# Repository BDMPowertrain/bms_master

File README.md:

<h1 align="center">BMS_MASTER</h1>
<p align="center">BMS Master</p>
<p align="center"><em>The BMS master board is the bridge between the TIM and the 16 BMS slave boards. It passes data both ways over a looped daisy chain, isolated by transformers so the battery’s high voltage never reaches the low-voltage side, and it signals the TIM the moment any slave reports a fault.</em></p>

<p align="center" width="100%">
  
</p>

***

<p align="center">
  
&nbsp; &nbsp; &nbsp; &nbsp;
  
</p>

***

## SPECIFICATIONS

| Parameter | Value |
| --- | --- |
| Dimensions | 100.0 × 50.0 mm |
| Company | Blue Devil Motor Sports |
| Designer | Aidan Brzezinski |
| Revision | + (Unreleased) |

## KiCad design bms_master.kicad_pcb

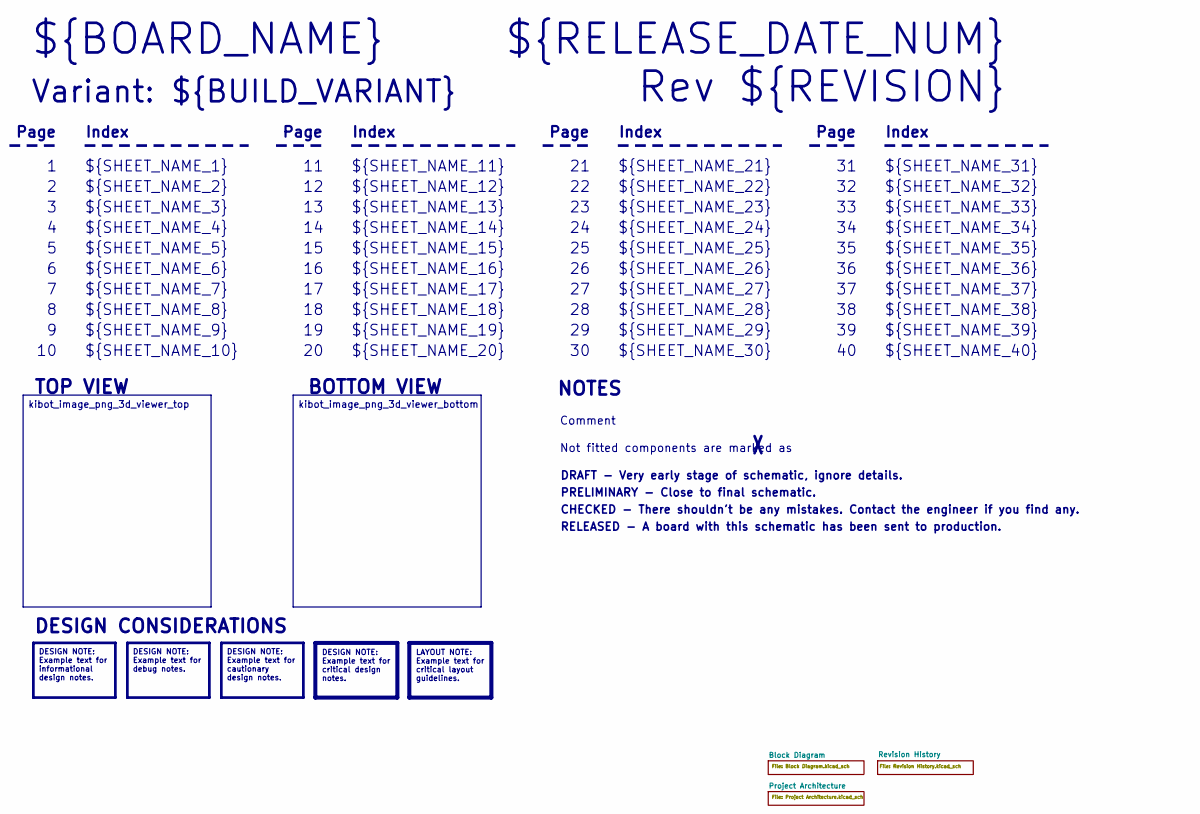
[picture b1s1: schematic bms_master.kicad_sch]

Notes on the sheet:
Variant: ${BUILD_VARIANT}
RELEASED - A board with this schematic has been sent to production.
${SHEET_NAME_24}
Index
Page
PRELIMINARY - Close to final schematic.
${SHEET_NAME_22}
DRAFT - Very early stage of schematic, ignore details.
${SHEET_NAME_12}
${SHEET_NAME_8}
${SHEET_NAME_2}
${SHEET_NAME_5}
${SHEET_NAME_20}
${SHEET_NAME_23}
${RELEASE_DATE_NUM}
${SHEET_NAME_35}
Not fitted components are marked as
${SHEET_NAME_11}
${SHEET_NAME_6}
${SHEET_NAME_37}
${SHEET_NAME_26}
${SHEET_NAME_36}
Rev ${REVISION}
${SHEET_NAME_15}
CHECKED - There shouldn't be any mistakes. Contact the engineer if you find any.
BOTTOM VIEW
${SHEET_NAME_14}
${SHEET_NAME_21}
${SHEET_NAME_17}
${SHEET_NAME_18}
${SHEET_NAME_7}
${SHEET_NAME_31}
${BOARD_NAME}
NOTES
${SHEET_NAME_40}
${SHEET_NAME_39}
${SHEET_NAME_32}
${SHEET_NAME_1}
${SHEET_NAME_9}
${SHEET_NAME_38}

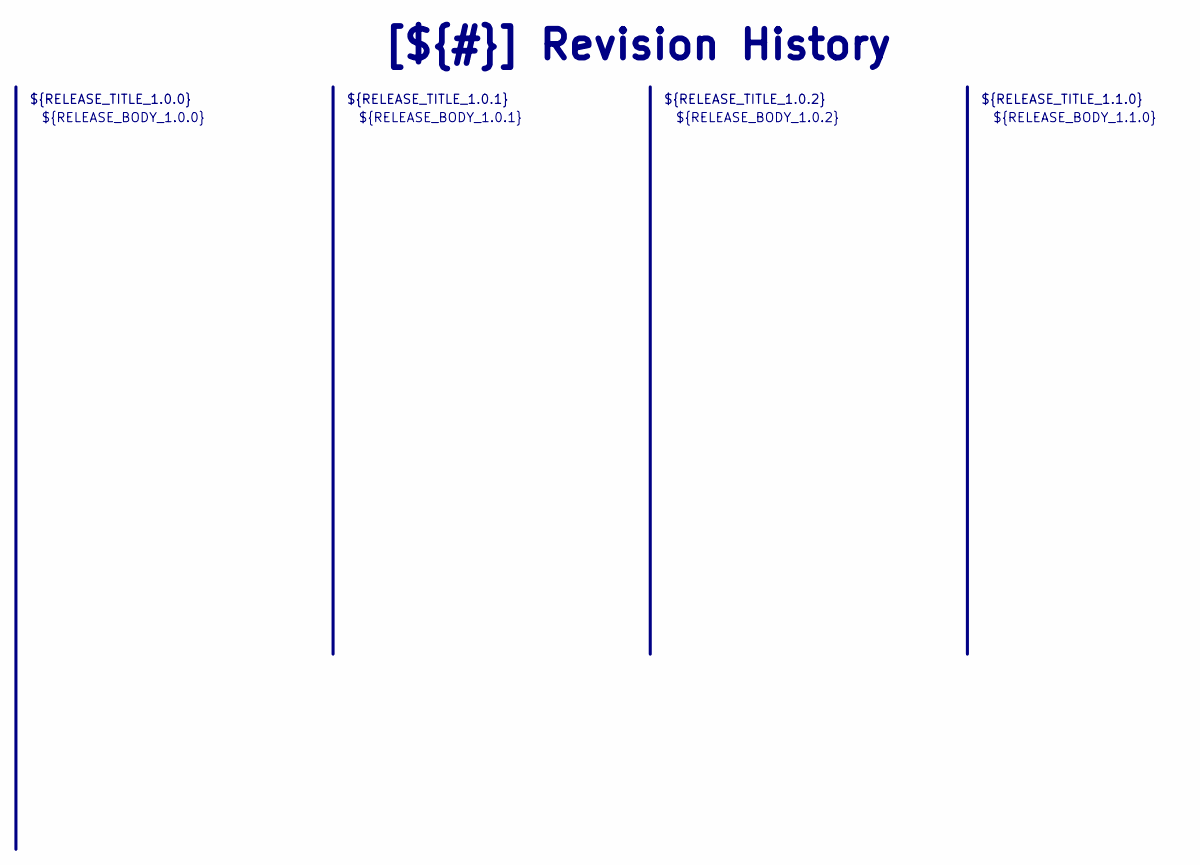
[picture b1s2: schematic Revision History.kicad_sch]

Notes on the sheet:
${RELEASE_BODY_1.1.0}
[${#}] ${TITLE}
${RELEASE_BODY_1.0.0}
${RELEASE_TITLE_1.0.2}
${RELEASE_BODY_1.0.2}
${RELEASE_BODY_1.0.1}
${RELEASE_TITLE_1.0.0}
${RELEASE_TITLE_1.0.1}
${RELEASE_TITLE_1.1.0}

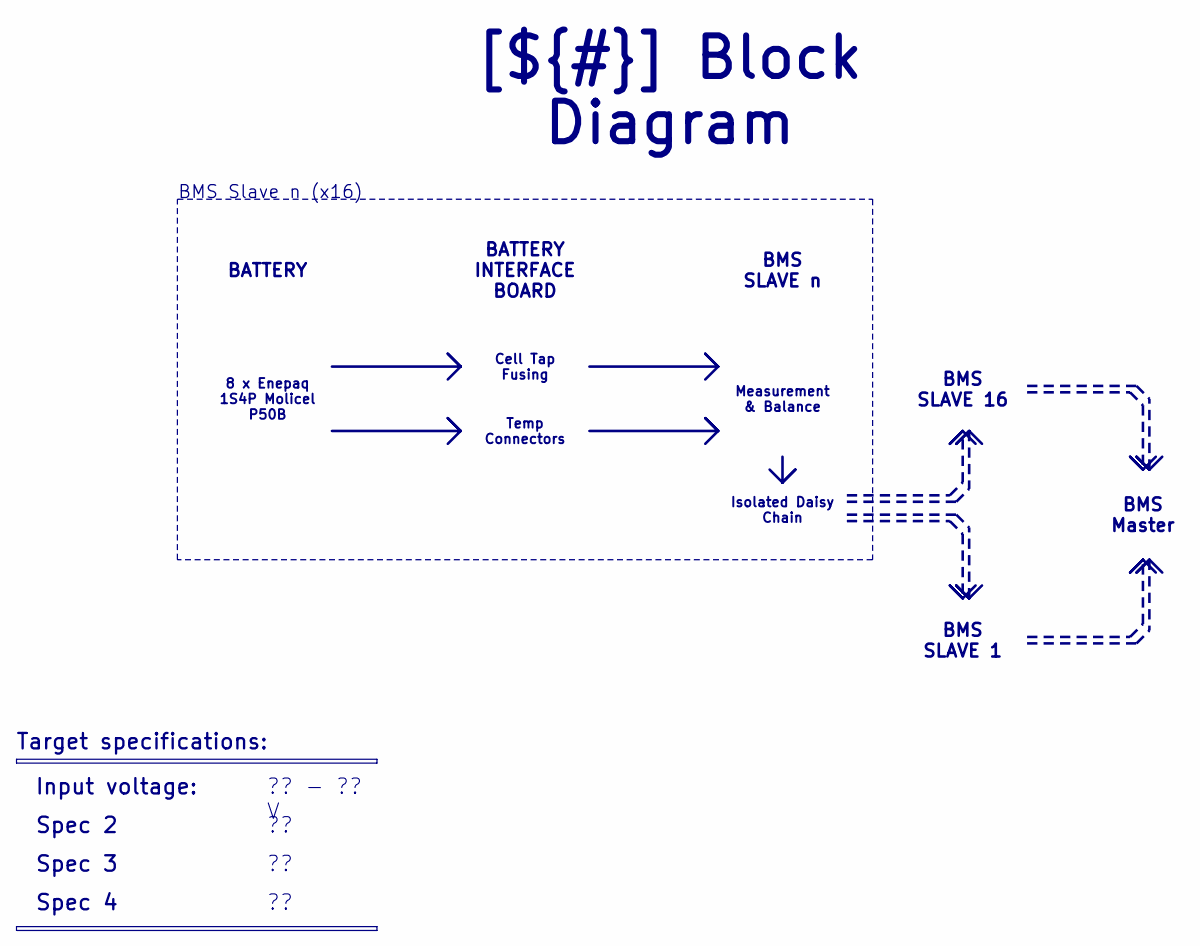
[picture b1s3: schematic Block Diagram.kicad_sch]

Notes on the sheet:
BMS Slave n (x16)
Spec 4
?? - ?? V
Isolated Daisy Chain
Cell Tap Fusing
8 x Enepaq 1S4P Molicel P50B
Temp Connectors
[${#}] ${TITLE}
Input voltage:
Target specifications:
BMS Master
Measurement & Balance
Spec 3
Spec 2
BATTERY
BMS SLAVE n
BMS SLAVE 16
BATTERY INTERFACE BOARD
BMS SLAVE 1

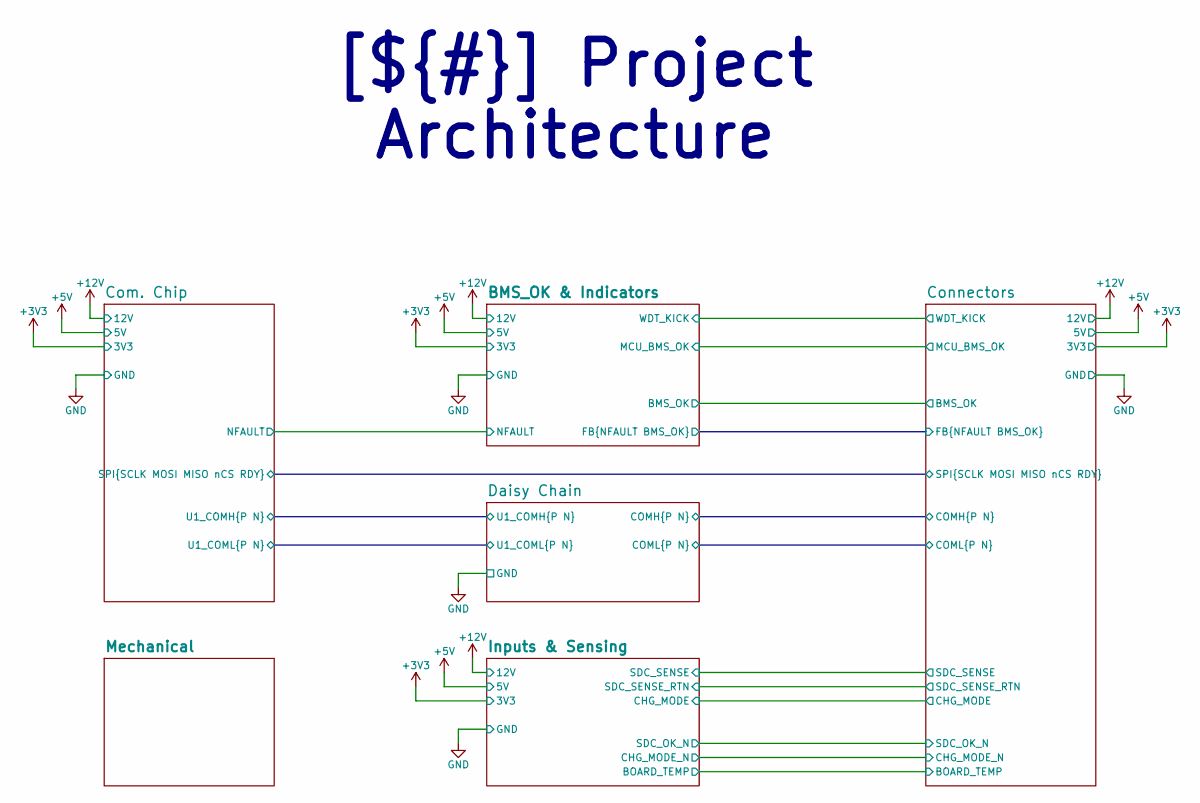
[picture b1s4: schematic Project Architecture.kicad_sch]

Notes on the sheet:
[${#}] ${TITLE}

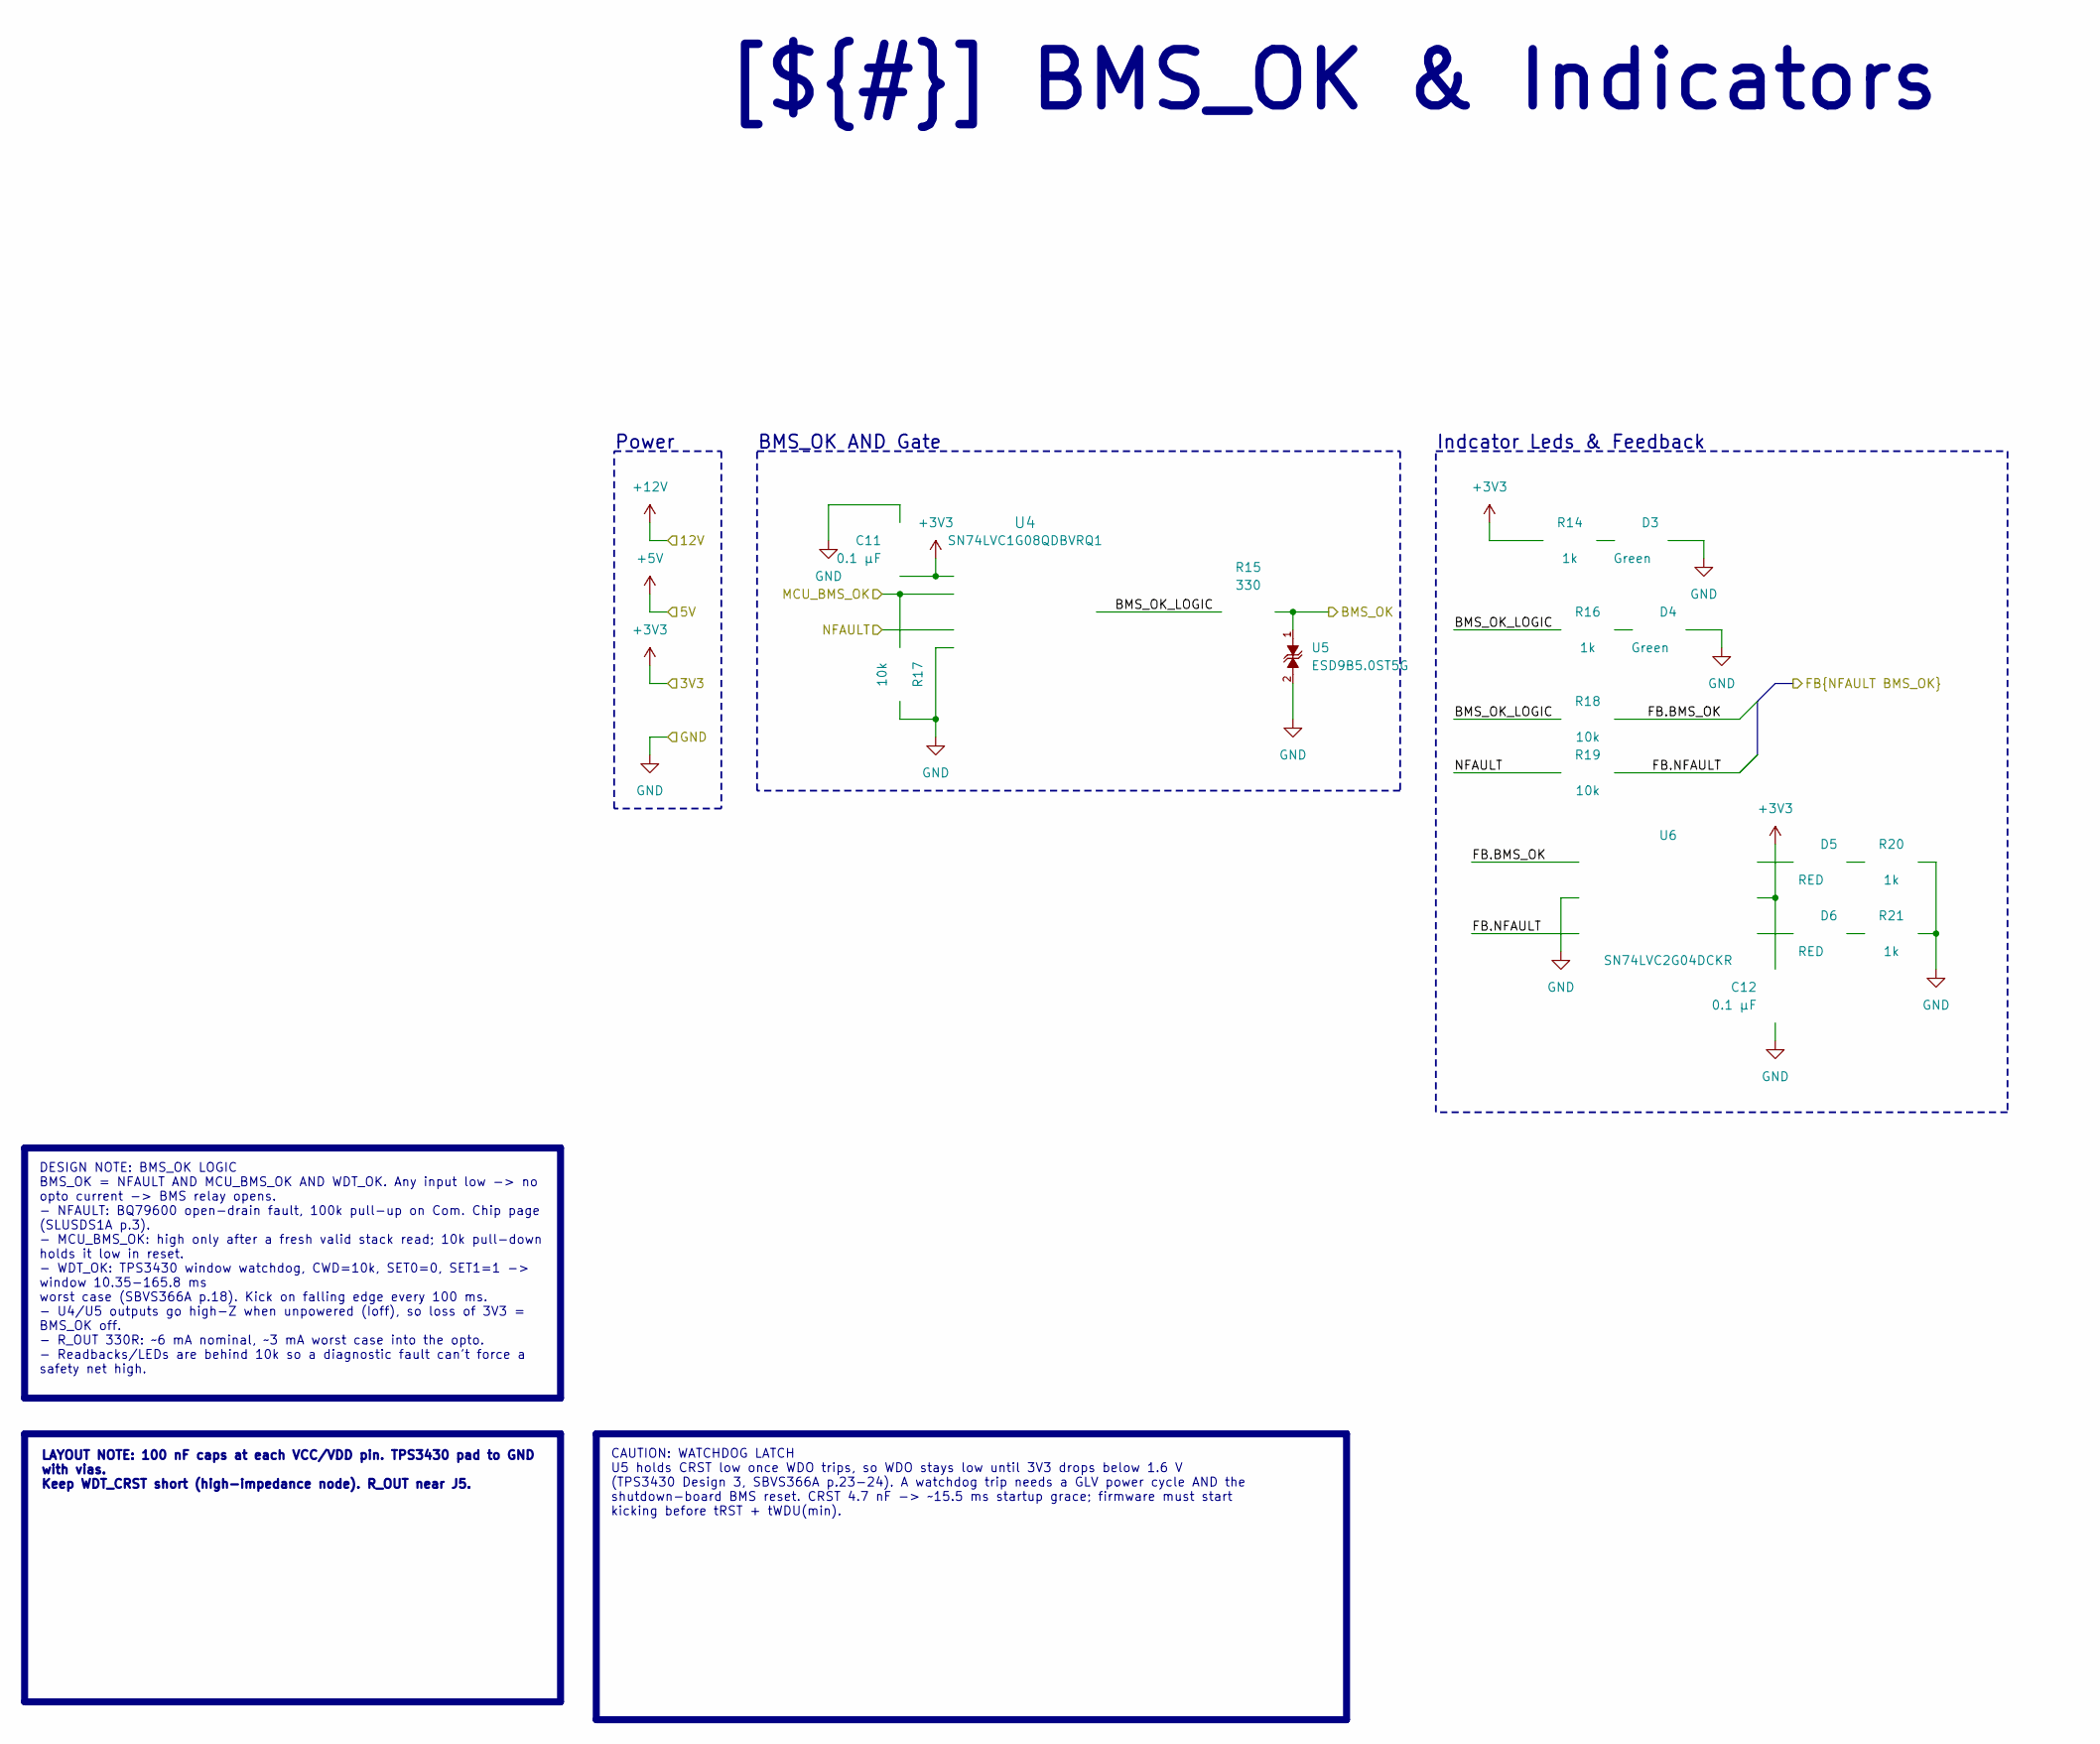
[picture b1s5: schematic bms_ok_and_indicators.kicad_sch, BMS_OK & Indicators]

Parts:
C11, C12: 0.1 µF; C_0402_1005Metric; Manufacturer Part Number GCM155R71H104KE02J
D3, D4: Green; LED_0603_1608Metric; Manufacturer Part Number LTST-C190KGKT
D5, D6: RED; LED_0603_1608Metric; Manufacturer Part Number LTST-C190KRKT
R14, R16, R20, R21: 1k; R_0402_1005Metric; Manufacturer Part Number ERJ-2RKF1001X
R15: 330; R_0805_2012Metric; Manufacturer Part Number CRCW0805330RFKEA
R17, R18, R19: 10k; R_0402_1005Metric; Manufacturer Part Number RC0402JR-0710KL
U4: SN74LVC1G08QDBVRQ1; DBV5; Manufacturer Part Number SN74LVC1G08QDBVRQ1
U5: ESD9B5.0ST5G; SODFL1006X40N; Manufacturer Part Number ESD9B5.0ST5G
U6: SN74LVC2G04DCKR; DCK0006A_N; Manufacturer Part Number SN74LVC2G04DCKR

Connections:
/Project Architecture/+3V3: C11.1, C12.2, R14.2, U4.5 (VCC), U6.5 (VCC); also elsewhere on the board
/Project Architecture/BMS_OK & Indicators/BMS_OK: R15.2, U5.1; also elsewhere on the board
/Project Architecture/BMS_OK & Indicators/BMS_OK_LOGIC: R15.1, R16.2, R18.1, U4.4 (Y)
/Project Architecture/BMS_OK & Indicators/FB.BMS_OK: R18.2, U6.1 (1A); also elsewhere on the board
/Project Architecture/BMS_OK & Indicators/FB.NFAULT: R19.2, U6.3 (2A); also elsewhere on the board
/Project Architecture/BMS_OK & Indicators/NFAULT: R19.1, U4.2 (B); also elsewhere on the board
/Project Architecture/Connectors/MCU_BMS_OK: R17.1, U4.1 (A); also elsewhere on the board
/Project Architecture/GND: C11.2, C12.1, D3.1 (K), D4.1 (K), R17.2, R20.1, R21.1, U4.3 (GND), U5.2, U6.2 (GND); also elsewhere on the board
unnamed: D3.2 (A), R14.1
unnamed: D4.2 (A), R16.1
unnamed: D5.2 (A), U6.6 (1Y)
unnamed: D5.1 (K), R20.2
unnamed: D6.2 (A), U6.4 (2Y)
unnamed: D6.1 (K), R21.2

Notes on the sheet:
BMS_OK AND Gate
Indcator Leds & Feedback
Power
[${#}] ${TITLE}
LAYOUT NOTE: 100 nF caps at each VCC/VDD pin. TPS3430 pad to GND with vias. Keep WDT_CRST short (high-impedance node). R_OUT near J5.
DESIGN NOTE: BMS_OK LOGIC BMS_OK = NFAULT AND MCU_BMS_OK AND WDT_OK. Any input low -> no opto current -> BMS relay opens. - NFAULT: BQ79600 open-drain fault, 100k pull-up on Com. Chip page (SLUSDS1A p.3). - MCU_BMS_OK: high only after a fresh valid stack read; 10k pull-down holds it low in reset. -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
CAUTION: WATCHDOG LATCH U5 holds CRST low once WDO trips, so WDO stays low until 3V3 drops below 1.6 V (TPS3430 Design 3, SBVS366A p.23-24). A watchdog trip needs a GLV power cycle AND the shutdown-board BMS reset. CRST 4.7 nF -> ~15.5 ms startup grace; firmware must start kicking before tRST + tWD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

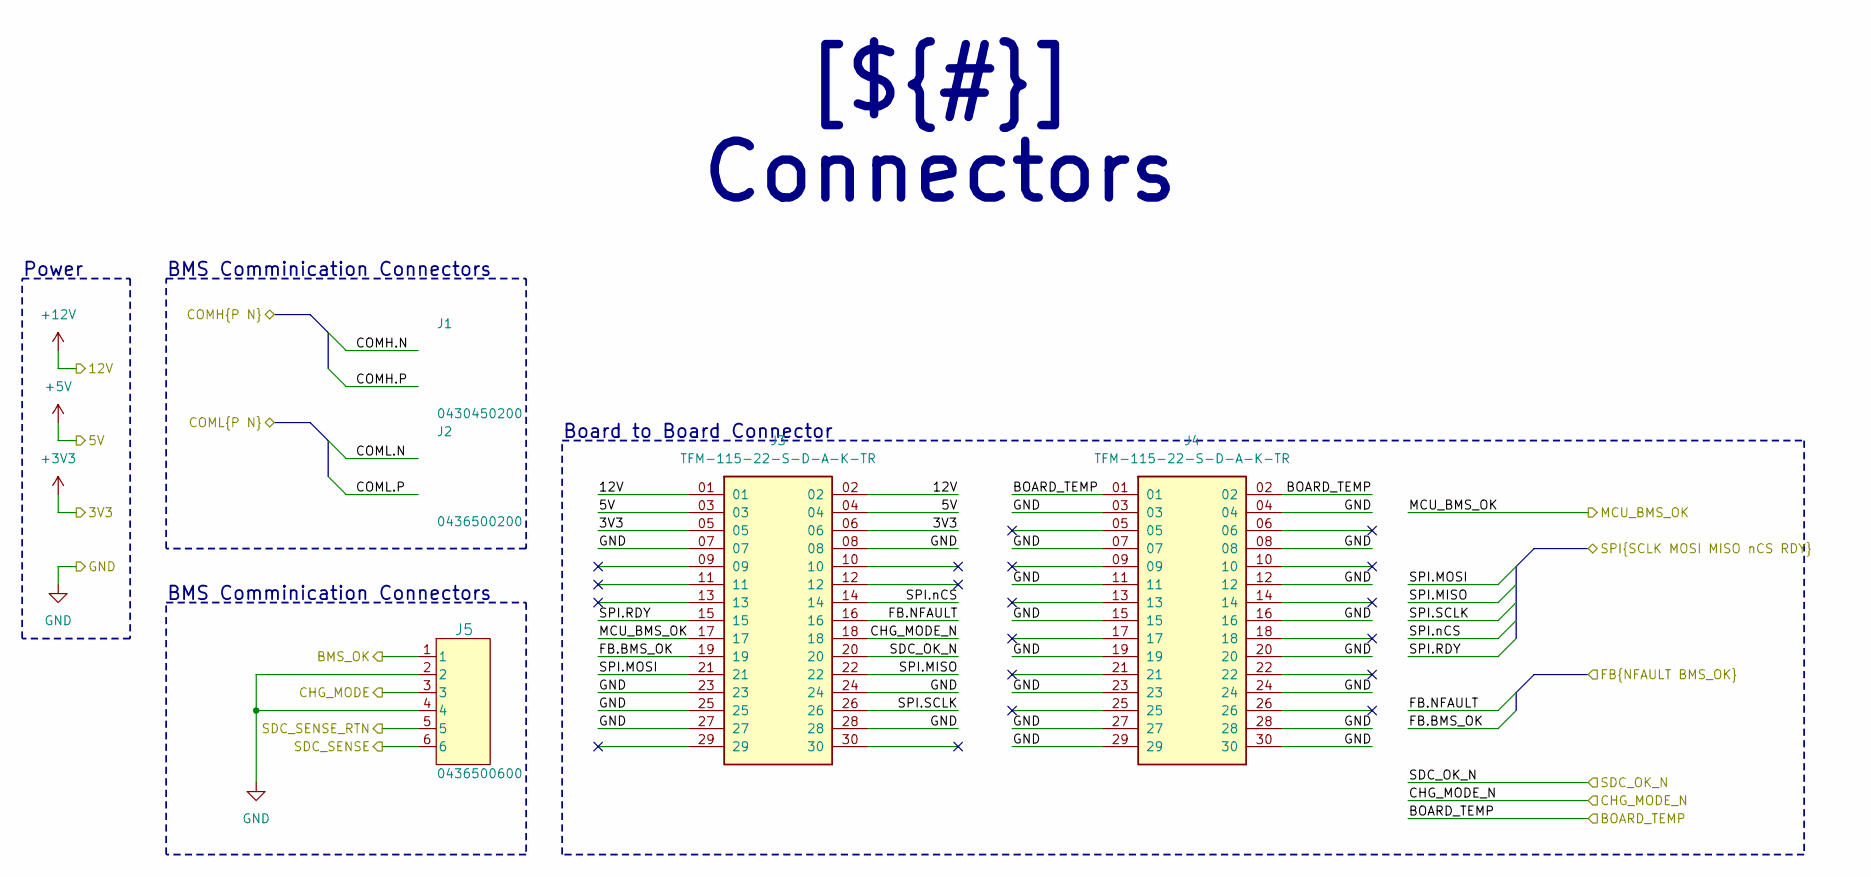
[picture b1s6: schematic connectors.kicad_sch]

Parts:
J1: 0430450200; CONN_SD-43045-001_02_MOL; Manufacturer Part Number 0430450200
J2: 0436500200; CONN_SD-43650-001_02_MOL; Manufacturer Part Number 0436500200
J3, J4: TFM-115-22-S-D-A-K-TR; SAMTEC_TFM-115-22-S-D-A; PARTREV R
J5: 0436500600; CONN_SD-43650-001_06_MOL; Manufacturer Part Number 0436500600

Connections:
/Project Architecture/+3V3: J3.05, J3.06; also elsewhere on the board
/Project Architecture/+5V: J3.03, J3.04
/Project Architecture/+12V: J3.01, J3.02; also elsewhere on the board
/Project Architecture/BMS_OK & Indicators/BMS_OK: J5.1; also elsewhere on the board
/Project Architecture/BMS_OK & Indicators/FB.BMS_OK: J3.19; also elsewhere on the board
/Project Architecture/BMS_OK & Indicators/FB.NFAULT: J3.16; also elsewhere on the board
/Project Architecture/Com. Chip/SPI.MISO: J3.22; also elsewhere on the board
/Project Architecture/Com. Chip/SPI.MOSI: J3.21; also elsewhere on the board
/Project Architecture/Com. Chip/SPI.RDY: J3.15; also elsewhere on the board
/Project Architecture/Com. Chip/SPI.SCLK: J3.26; also elsewhere on the board
/Project Architecture/Com. Chip/SPI.nCS: J3.14; also elsewhere on the board
/Project Architecture/Connectors/BOARD_TEMP: J4.01, J4.02; also elsewhere on the board
/Project Architecture/Connectors/CHG_MODE: J5.3; also elsewhere on the board
/Project Architecture/Connectors/CHG_MODE_N: J3.18; also elsewhere on the board
/Project Architecture/Connectors/COMH.N: J1.1; also elsewhere on the board
/Project Architecture/Connectors/COMH.P: J1.2; also elsewhere on the board
/Project Architecture/Connectors/COML.N: J2.1; also elsewhere on the board
/Project Architecture/Connectors/COML.P: J2.2; also elsewhere on the board
/Project Architecture/Connectors/MCU_BMS_OK: J3.17; also elsewhere on the board
/Project Architecture/Connectors/SDC_OK_N: J3.20; also elsewhere on the board
/Project Architecture/Connectors/SDC_SENSE: J5.6; also elsewhere on the board
/Project Architecture/Connectors/SDC_SENSE_RTN: J5.5; also elsewhere on the board
/Project Architecture/GND: J3.07, J3.08, J3.23, J3.24, J3.25, J3.27, J3.28, J4.03, J4.04, J4.07, J4.08, J4.11, J4.12, J4.15, J4.16, J4.19, J4.20, J4.23, J4.24, J4.27, J4.28, J4.29, J4.30, J5.2, J5.4; also elsewhere on the board

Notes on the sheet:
Power
BMS Comminication Connectors
Board to Board Connector
[${#}] ${TITLE}

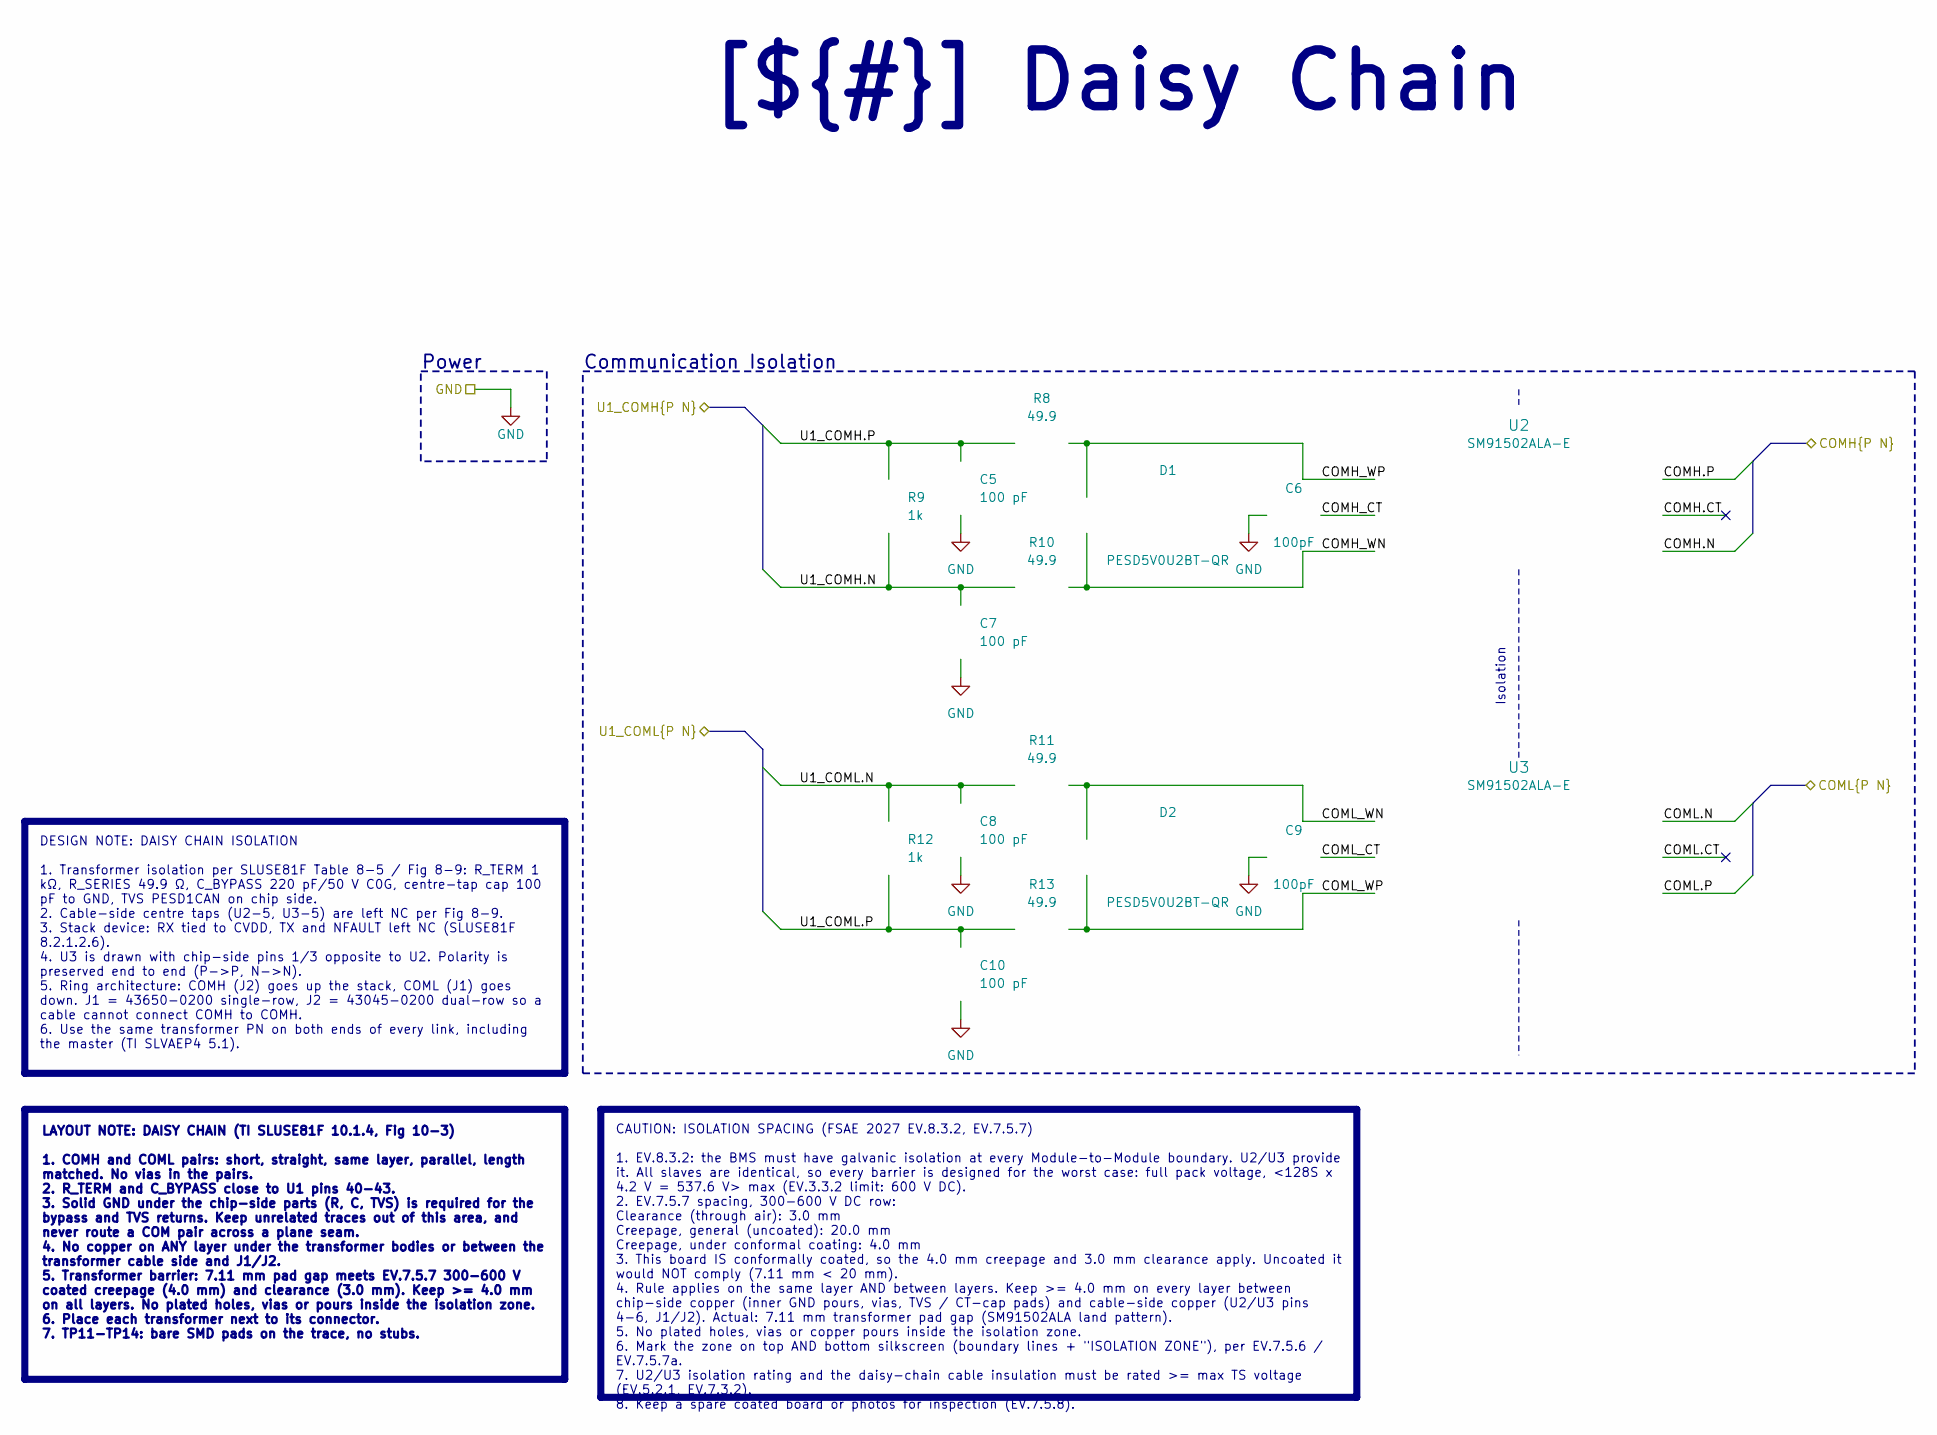
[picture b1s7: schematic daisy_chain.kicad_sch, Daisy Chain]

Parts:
C5, C7, C8, C10: 100 pF; C_0402_1005Metric; Manufacturer Part Number GCM1555C1H101JA16D
C6, C9: 100pF; C_0402_1005Metric; Manufacturer Part Number GCM1555C1H101JA16D
D1, D2: PESD5V0U2BT-QR; SOT-23-3; Manufacturer Part Number PESD5V0U2BT-QR
R8, R10, R11, R13: 49.9; R_0402_1005Metric; Manufacturer Part Number CRCW040249R9FKED
R9, R12: 1k; R_0402_1005Metric; Manufacturer Part Number ERJ-2RKF1001X
U2, U3: SM91502ALA-E; IC6_SM91502ALA-E_BRN; Manufacturer Part Number SM91502ALA-E

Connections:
/Project Architecture/Com. Chip/U1_COMH.N: C7.2, R9.2, R10.1; also elsewhere on the board
/Project Architecture/Com. Chip/U1_COMH.P: C5.2, R8.1, R9.1; also elsewhere on the board
/Project Architecture/Com. Chip/U1_COML.N: C8.2, R11.1, R12.1; also elsewhere on the board
/Project Architecture/Com. Chip/U1_COML.P: C10.2, R12.2, R13.1; also elsewhere on the board
/Project Architecture/Connectors/COMH.N: U2.4; also elsewhere on the board
/Project Architecture/Connectors/COMH.P: U2.6; also elsewhere on the board
/Project Architecture/Connectors/COML.N: U3.6; also elsewhere on the board
/Project Architecture/Connectors/COML.P: U3.4; also elsewhere on the board
/Project Architecture/Daisy Chain/COMH.CT: U2.5
/Project Architecture/Daisy Chain/COMH_CT: C6.1, U2.2
/Project Architecture/Daisy Chain/COMH_WN: D1.2, R10.2, U2.3
/Project Architecture/Daisy Chain/COMH_WP: D1.1, R8.2, U2.1
/Project Architecture/Daisy Chain/COML.CT: U3.5
/Project Architecture/Daisy Chain/COML_CT: C9.1, U3.2
/Project Architecture/Daisy Chain/COML_WN: D2.1, R11.2, U3.1
/Project Architecture/Daisy Chain/COML_WP: D2.2, R13.2, U3.3
/Project Architecture/GND: C5.1, C6.2, C7.1, C8.1, C9.2, C10.1, D1.3, D2.3; also elsewhere on the board

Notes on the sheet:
Isolation
Communication Isolation
Power
[${#}] ${TITLE}
CAUTION: ISOLATION SPACING (FSAE 2027 EV.8.3.2, EV.7.5.7) 1. EV.8.3.2: the BMS must have galvanic isolation at every Module-to-Module boundary. U2/U3 provide it. All slaves are identical, so every barrier is designed for the worst case: full pack voltage, <128S x 4.2 V = 537.6 V> max (EV.3.3.2 limi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
DESIGN NOTE: DAISY CHAIN ISOLATION 1. Transformer isolation per SLUSE81F Table 8-5 / Fig 8-9: R_TERM 1 kΩ, R_SERIES 49.9 Ω, C_BYPASS 220 pF/50 V C0G, centre-tap cap 100 pF to GND, TVS PESD1CAN on chip side. 2. Cable-side centre taps (U2-5, U3-5) are left NC per Fig 8-9. 3. Stack device: RX tied to 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
LAYOUT NOTE: DAISY CHAIN (TI SLUSE81F 10.1.4, Fig 10-3) 1. COMH and COML pairs: short, straight, same layer, parallel, length matched. No vias in the pairs. 2. R_TERM and C_BYPASS close to U1 pins 40-43. 3. Solid GND under the chip-side parts (R, C, TVS) is required for the bypass and TVS returns. 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

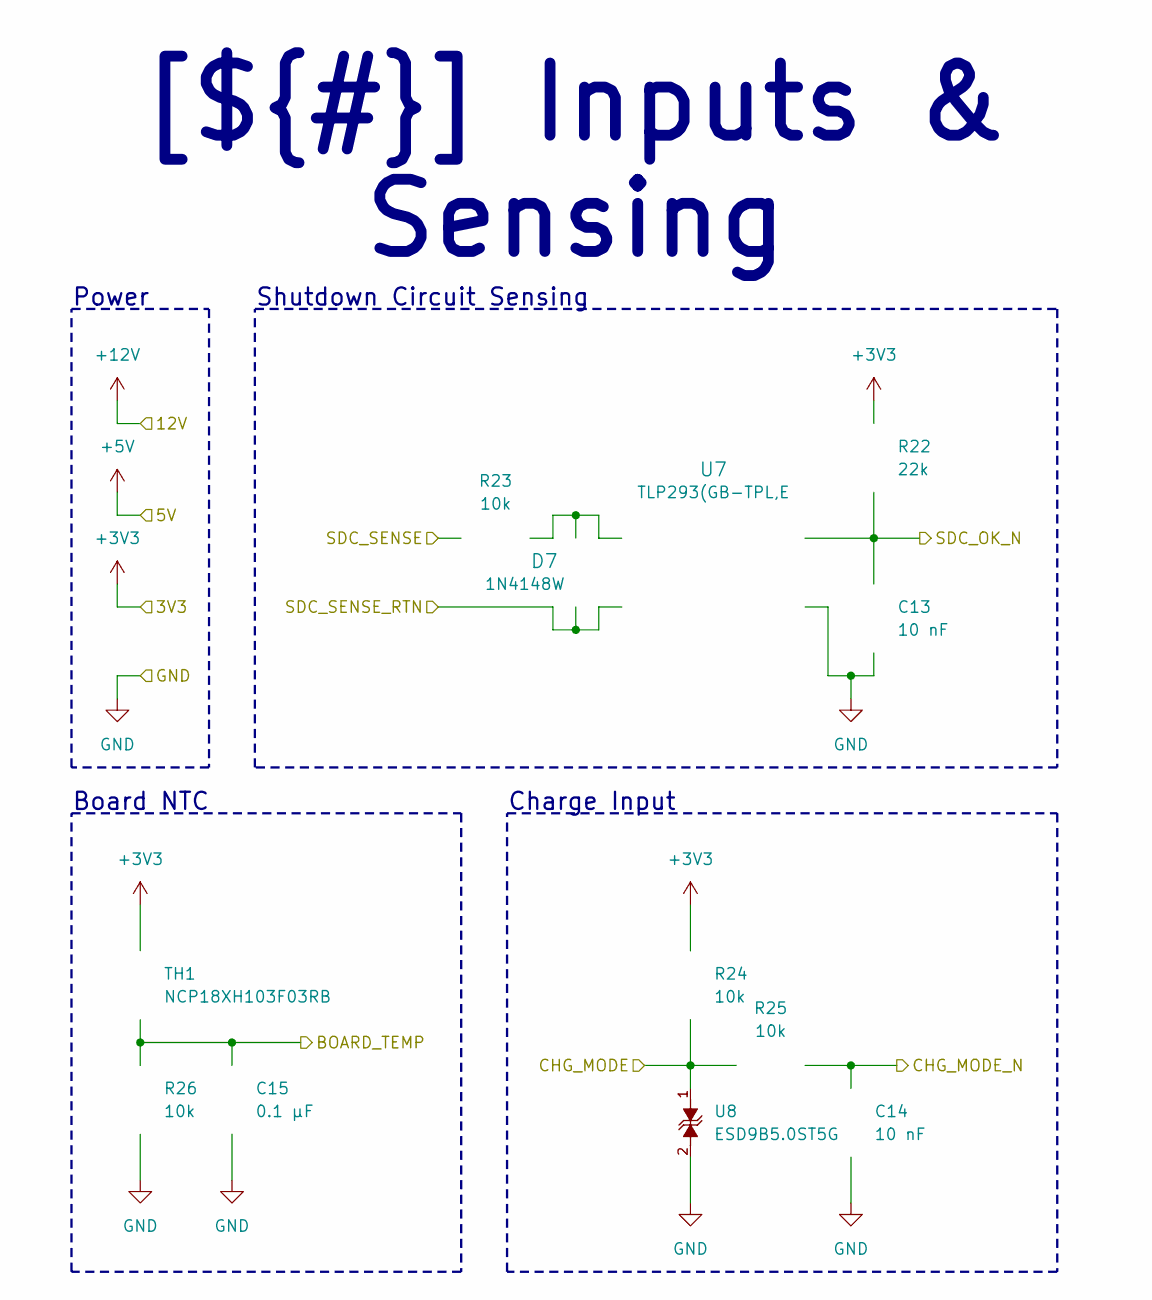
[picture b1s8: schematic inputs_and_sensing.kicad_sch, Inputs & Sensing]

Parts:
C13, C14: 10 nF; C_0402_1005Metric; Manufacturer Part Number C0402C103K5RECAUTO
C15: 0.1 µF; C_0402_1005Metric; Manufacturer Part Number GCM155R71H104KE02J
D7: 1N4148W; P35_SOD-123F; Manufacturer Part Number 1N4148W
R22: 22k; R_0603_1608Metric; Manufacturer Part Number CRCW060322K0FKEA
R23: 10k; R_0805_2012Metric; Manufacturer Part Number CRCW080510K0FKEA
R24, R25, R26: 10k; R_0603_1608Metric; Manufacturer Part Number CRCW060310K0FKEA
TH1: NCP18XH103F03RB; R_0603_1608Metric; Manufacturer Part Number NCP18XH103F03RB
U7: TLP293(GB-TPL,E; SO4_TOS; Manufacturer Part Number TLP293(GB-TPL,E
U8: ESD9B5.0ST5G; SODFL1006X40N; Manufacturer Part Number ESD9B5.0ST5G

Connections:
/Project Architecture/+3V3: R22.2, R24.2, TH1.1; also elsewhere on the board
/Project Architecture/Connectors/BOARD_TEMP: C15.2, R26.2, TH1.2; also elsewhere on the board
/Project Architecture/Connectors/CHG_MODE: R24.1, R25.1, U8.1; also elsewhere on the board
/Project Architecture/Connectors/CHG_MODE_N: C14.1, R25.2; also elsewhere on the board
/Project Architecture/Connectors/SDC_OK_N: C13.1, R22.1, U7.4; also elsewhere on the board
/Project Architecture/Connectors/SDC_SENSE: R23.1; also elsewhere on the board
/Project Architecture/Connectors/SDC_SENSE_RTN: D7.2 (A), U7.2; also elsewhere on the board
/Project Architecture/GND: C13.2, C14.2, C15.1, R26.1, U7.3, U8.2; also elsewhere on the board
unnamed: D7.1 (K), R23.2, U7.1

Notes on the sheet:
Charge Input
Power
Shutdown Circuit Sensing
Board NTC
[${#}] ${TITLE}

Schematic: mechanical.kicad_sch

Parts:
FID1, FID2, FID3: Fiducial; Fiducial_0.5mm_Mask1mm
G1: SAE Electric logo; SAE_Electric_Logo_10mm; Manufacturer Part Number SAE Electric logo
G2: BMD Logo; BDM_Logo_100mm; Manufacturer Part Number BMD Logo
H1, H2, H3, H4, H5: MountingHole; MountingHole_3.2mm_M3

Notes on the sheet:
Silkscreen
Fiducials
Mounting Holes
[${#}] ${TITLE}

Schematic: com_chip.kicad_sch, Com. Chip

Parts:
C1, C4: 220 nF; C_0402_1005Metric; Manufacturer Part Number GRM155R61H224KE01D
C2, C3: 0.1 µF; C_0402_1005Metric; Manufacturer Part Number GCM155R71H104KE02J
R1: 10; R_0603_1608Metric; Manufacturer Part Number CRCW060310R0JNEA
R2: 100k; R_0603_1608Metric; Manufacturer Part Number CRCW0603100KFKEA
R3, R4, R7: 10k; R_0402_1005Metric; Manufacturer Part Number RC0402JR-0710KL
R5, R6: 10k; R_0402_1005Metric; Manufacturer Part Number RC0402JR-0710KL; not fitted
U1: BQ79600PWRQ1; SOIC_9600PWQ1_TEX; Manufacturer Part Number BQ79600PWRQ1

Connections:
/Project Architecture/+3V3: C3.1, R2.2, R3.2, R4.2, R5.2, R6.2, U1.3 (VIO); also elsewhere on the board
/Project Architecture/+12V: R1.2; also elsewhere on the board
/Project Architecture/BMS_OK & Indicators/NFAULT: R2.1, U1.2 (NFAULT); also elsewhere on the board
/Project Architecture/Com. Chip/BAT: C2.1, R1.1, U1.15 (BAT), U1.16 (INH)
/Project Architecture/Com. Chip/CVDD: C4.1, U1.14 (CVDD)
/Project Architecture/Com. Chip/DVDD: C1.2, U1.1 (DVDD)
/Project Architecture/Com. Chip/SPI.MISO: R6.1, U1.5 (MISO/RX); also elsewhere on the board
/Project Architecture/Com. Chip/SPI.MOSI: R5.1, U1.4 (MOSI/RX); also elsewhere on the board
/Project Architecture/Com. Chip/SPI.RDY: R4.1, U1.8 (nUART/SPI); also elsewhere on the board
/Project Architecture/Com. Chip/SPI.SCLK: R7.2, U1.6 (SCLK); also elsewhere on the board
/Project Architecture/Com. Chip/SPI.nCS: R3.1, U1.7 (nCS); also elsewhere on the board
/Project Architecture/Com. Chip/U1_COMH.N: U1.12 (COMHN); also elsewhere on the board
/Project Architecture/Com. Chip/U1_COMH.P: U1.13 (COMHP); also elsewhere on the board
/Project Architecture/Com. Chip/U1_COML.N: U1.11 (COMLN); also elsewhere on the board
/Project Architecture/Com. Chip/U1_COML.P: U1.10 (COMLP); also elsewhere on the board
/Project Architecture/GND: C1.1, C2.2, C3.2, C4.2, R7.1, U1.9 (GND); also elsewhere on the board

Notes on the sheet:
Master Com. Chip
Power
[${#}] ${TITLE}
